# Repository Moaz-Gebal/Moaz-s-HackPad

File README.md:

# MACRO5000
- - -

This MacroPad features 10 MX Switches, a 0.96 inch screen, and a rotary encoder. Every part has its own purpose
- - -
# CAD
---
This HackPad Has A fun little aesthetic in where you can see the brains of the keyboard working to help you in your needs, it was made in SolidWorks. I used heatset inserts for 4x M3x16mm screws in a sandwich type of assembly.   Looks like the sky. 

- - -
# PCP
---
The PCP, contains our Seeed Studio XIAO RP2040 and all the switches you would need, plus a rotary encoder. Was made in KiCad 

| | PCP                                    |
| ------------------------------------ | -------------------------------------- |
| | <font color="#ccc1d9">SCHEMATIC</font> |
- - -
# Firmware
- - -
I used [QMK](https://qmk.fm/) . Have two layers, first is a normal numpad, the second is for macros that I would as I want. Encoder controls volume and the screen contains which layer I am on.
- - -
# BOM
---
- 1x  Seeed Studio XIAO RP2040
- 10x 1N4148 Diodes
- 10x MX-Style switches
- 1x EC11 Rotary encoders
- 1x 0.91 inch OLED display
- 10x white blank DSA keycaps
- 4x M3x16mm screws
- 4x M3x5mx4mm heatset inserts
- 1x Case (2 3d printed parts; top and bottom)

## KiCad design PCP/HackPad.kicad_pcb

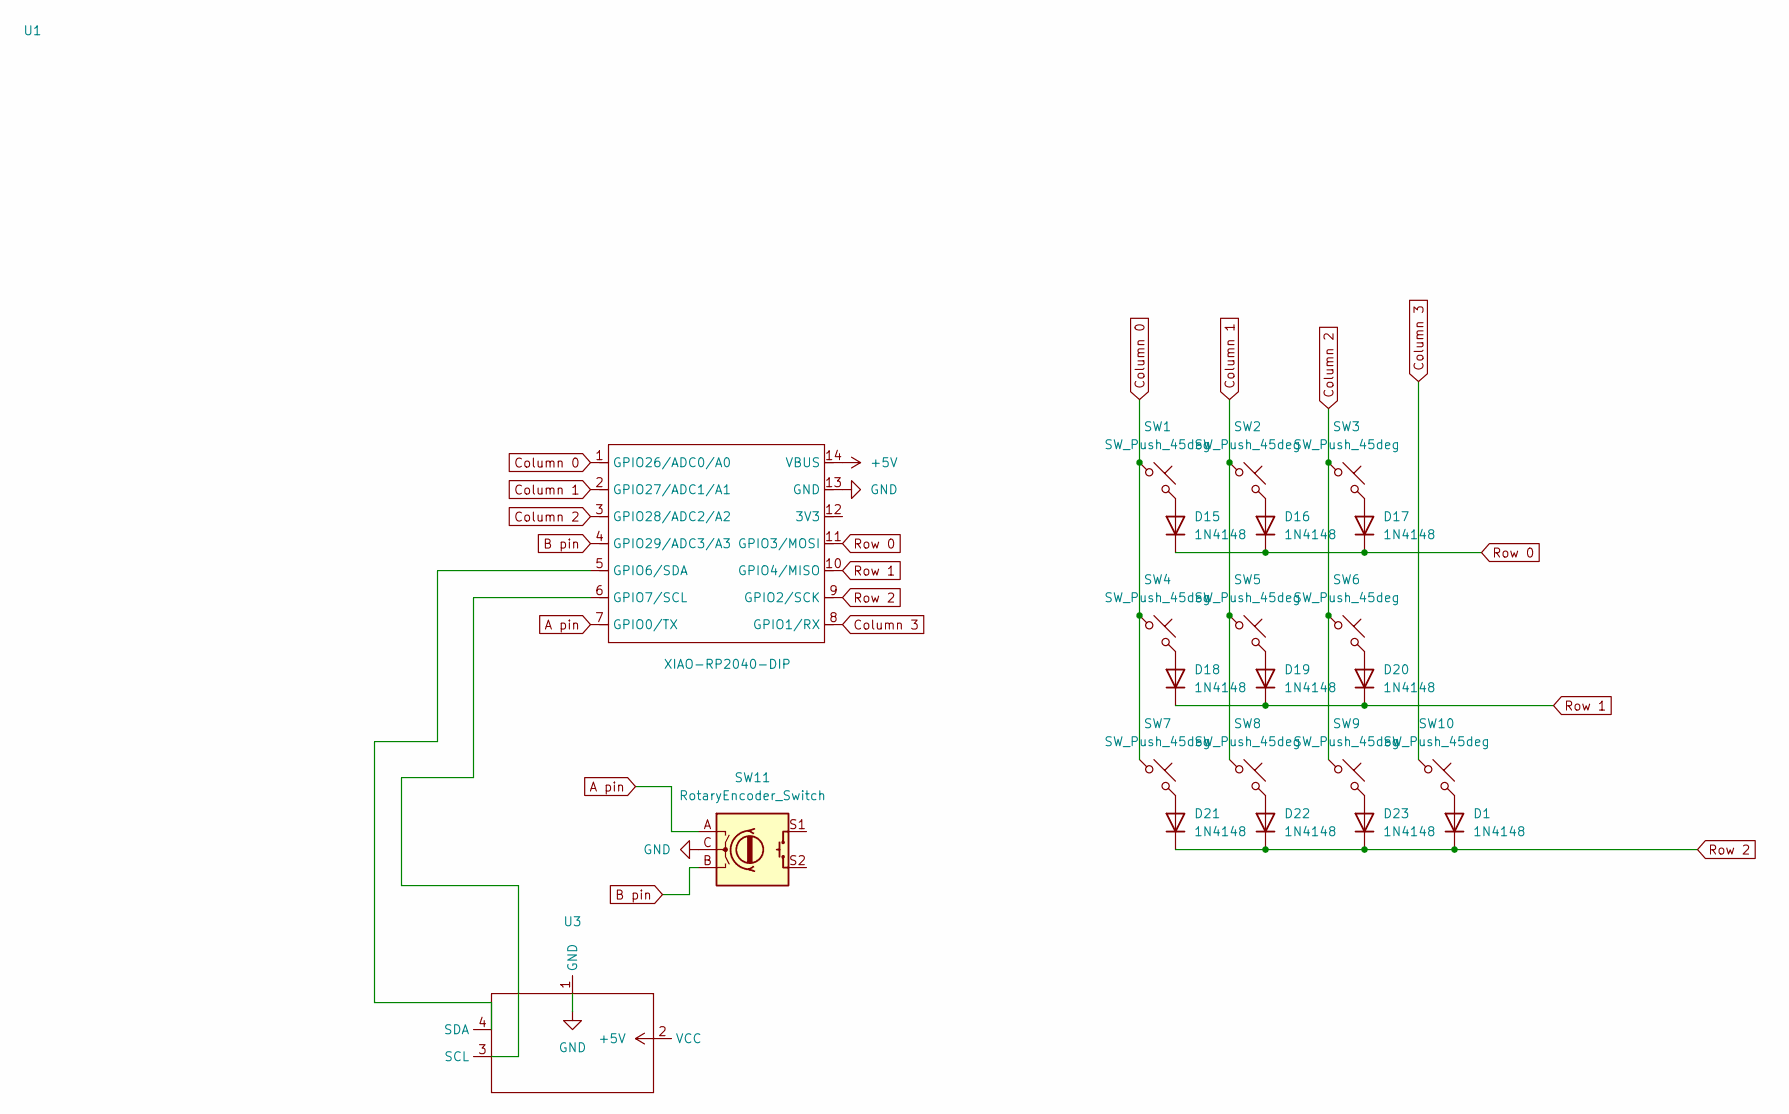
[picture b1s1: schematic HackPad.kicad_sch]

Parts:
D1, D15, D16, D17, D18, D19, D20, D21, D22, D23: 1N4148; D_DO-35_SOD27_P7.62mm_Horizontal
SW1, SW2, SW3, SW4, SW5, SW6, SW7, SW8, SW9, SW10: SW_Push_45deg; SW_Cherry_MX_1.00u_PCB
SW11: RotaryEncoder_Switch; RotaryEncoder_Alps_EC11E-Switch_Vertical_H20mm
U1: XIAO-RP2040-DIP
U3: SSD1306-0.91-OLED-4pin-128x32

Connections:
+5V: U1.14 (VBUS), U3.2 (VCC)
A pin: SW11.A, U1.7 (GPIO0/TX)
B pin: SW11.B, U1.4 (GPIO29/ADC3/A3)
Column 0: SW1.1, SW4.1, SW7.1, U1.1 (GPIO26/ADC0/A0)
Column 1: SW2.1, SW5.1, SW8.1, U1.2 (GPIO27/ADC1/A1)
Column 2: SW3.1, SW6.1, SW9.1, U1.3 (GPIO28/ADC2/A2)
Column 3: SW10.1, U1.8 (GPIO1/RX)
GND: SW11.C, U1.13 (GND), U3.1 (GND)
unnamed: D1.2 (A), SW10.2
unnamed: D15.2 (A), SW1.2
unnamed: D16.2 (A), SW2.2
unnamed: D17.2 (A), SW3.2
unnamed: D18.2 (A), SW4.2
unnamed: D19.2 (A), SW5.2
unnamed: D20.2 (A), SW6.2
unnamed: D21.2 (A), SW7.2
unnamed: D22.2 (A), SW8.2
unnamed: D23.2 (A), SW9.2
unnamed: U1.5 (GPIO6/SDA), U3.4 (SDA)
unnamed: U1.6 (GPIO7/SCL), U3.3 (SCL)
Row 0: D15.1 (K), D16.1 (K), D17.1 (K), U1.11 (GPIO3/MOSI)
Row 1: D18.1 (K), D19.1 (K), D20.1 (K), U1.10 (GPIO4/MISO)
Row 2: D1.1 (K), D21.1 (K), D22.1 (K), D23.1 (K), U1.9 (GPIO2/SCK)

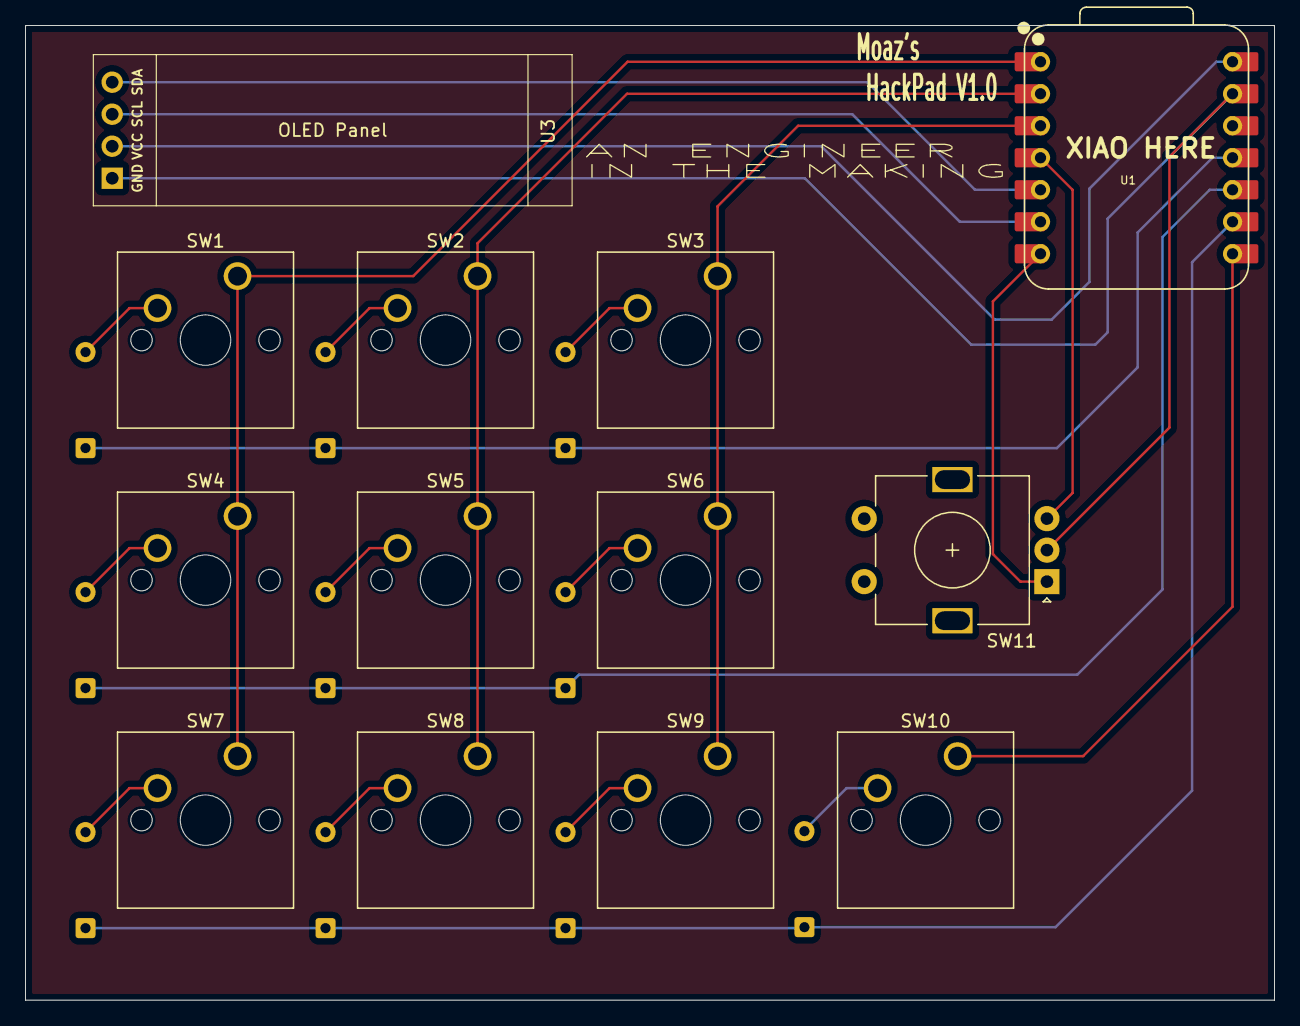
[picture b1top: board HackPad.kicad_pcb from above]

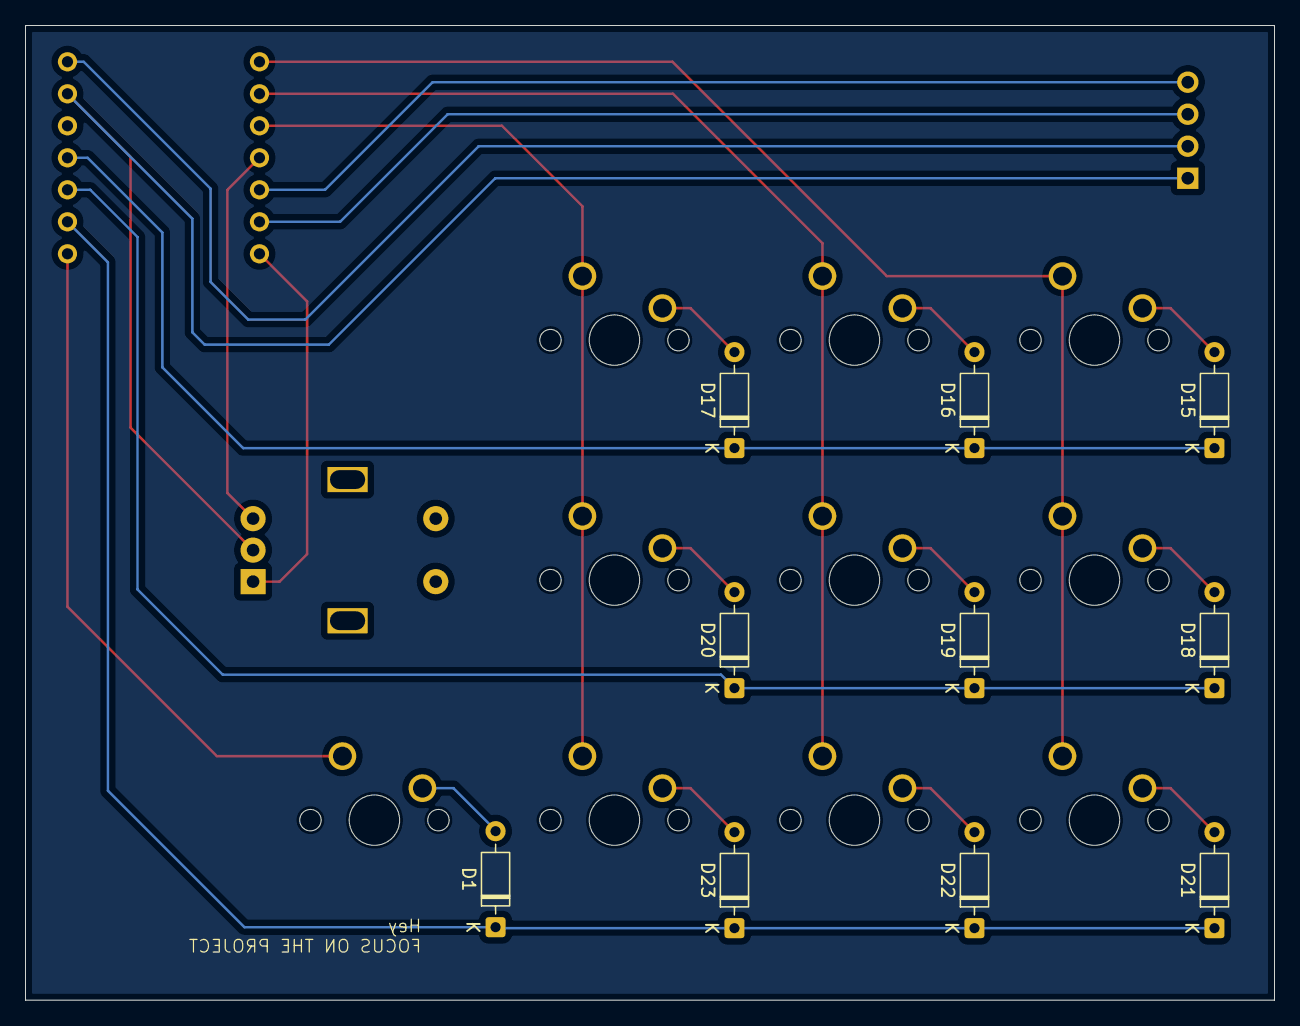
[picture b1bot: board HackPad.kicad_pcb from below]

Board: 2 copper layers, 99.1 x 77.4 mm, 23 parts (10 on the bottom side), 23 nets.

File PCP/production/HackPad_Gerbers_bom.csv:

Designator,Footprint,Quantity,Value,LCSC Part #
"D1, D15, D16, D17, D18, D19, D20, D21, D22, D23",D_DO-35_SOD27_P7.62mm_Horizontal,10,1N4148,
"SW1, SW10, SW2, SW3, SW4, SW5, SW6, SW7, SW8, SW9",SW_Cherry_MX_1.00u_PCB,10,SW_Push_45deg,
SW11,RotaryEncoder_Alps_EC11E-Switch_Vertical_H20mm,1,RotaryEncoder_Switch,
U1,XIAO-RP2040-DIP,1,XIAO-RP2040-DIP,
U3,SSD1306-0.91-OLED-4pin-128x32,1,~,

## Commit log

2026-03-12 Delete Assembly.STEP
    Put it in the wrong directory
2026-03-15 Adding source CAD files
